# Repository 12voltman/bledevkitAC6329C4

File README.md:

# Dev board for the AC6329C4 from JieLi Tech
Able to be found for an astounding $0.25 in quantity [here](https://www.lcsc.com/product-detail/Microcontroller-Units-MCUs-MPUs-SOCs_JieLi-Tech-AC6329C4_C5440081.html), the AC6329C4 is a promising chip for ultra low cost BLE devices.  
Some of the cool features of this chip:  
- Integrated battery charger
- Integrated LDO for powering peripherals
- BLE 5.3 (may support further with new firmware)
- Full-speed USB OTG with built-in bootloader (needs weird trigger to enter DFU)
- 3 UARTs
- 1 I<sup>2</sup>C
- RTC
- 10-bit ADC w/ 6 channels
## Dev board features
This chip has some oddities around the bootloader, which needs a very specific bit pattern to be presented on the USB lines to enter DFU mode.  To enter DFU mode, I added an ATTINY microcontroller and a USB isolation switch, which also lets you use the USB pins as extra IOs if desired.

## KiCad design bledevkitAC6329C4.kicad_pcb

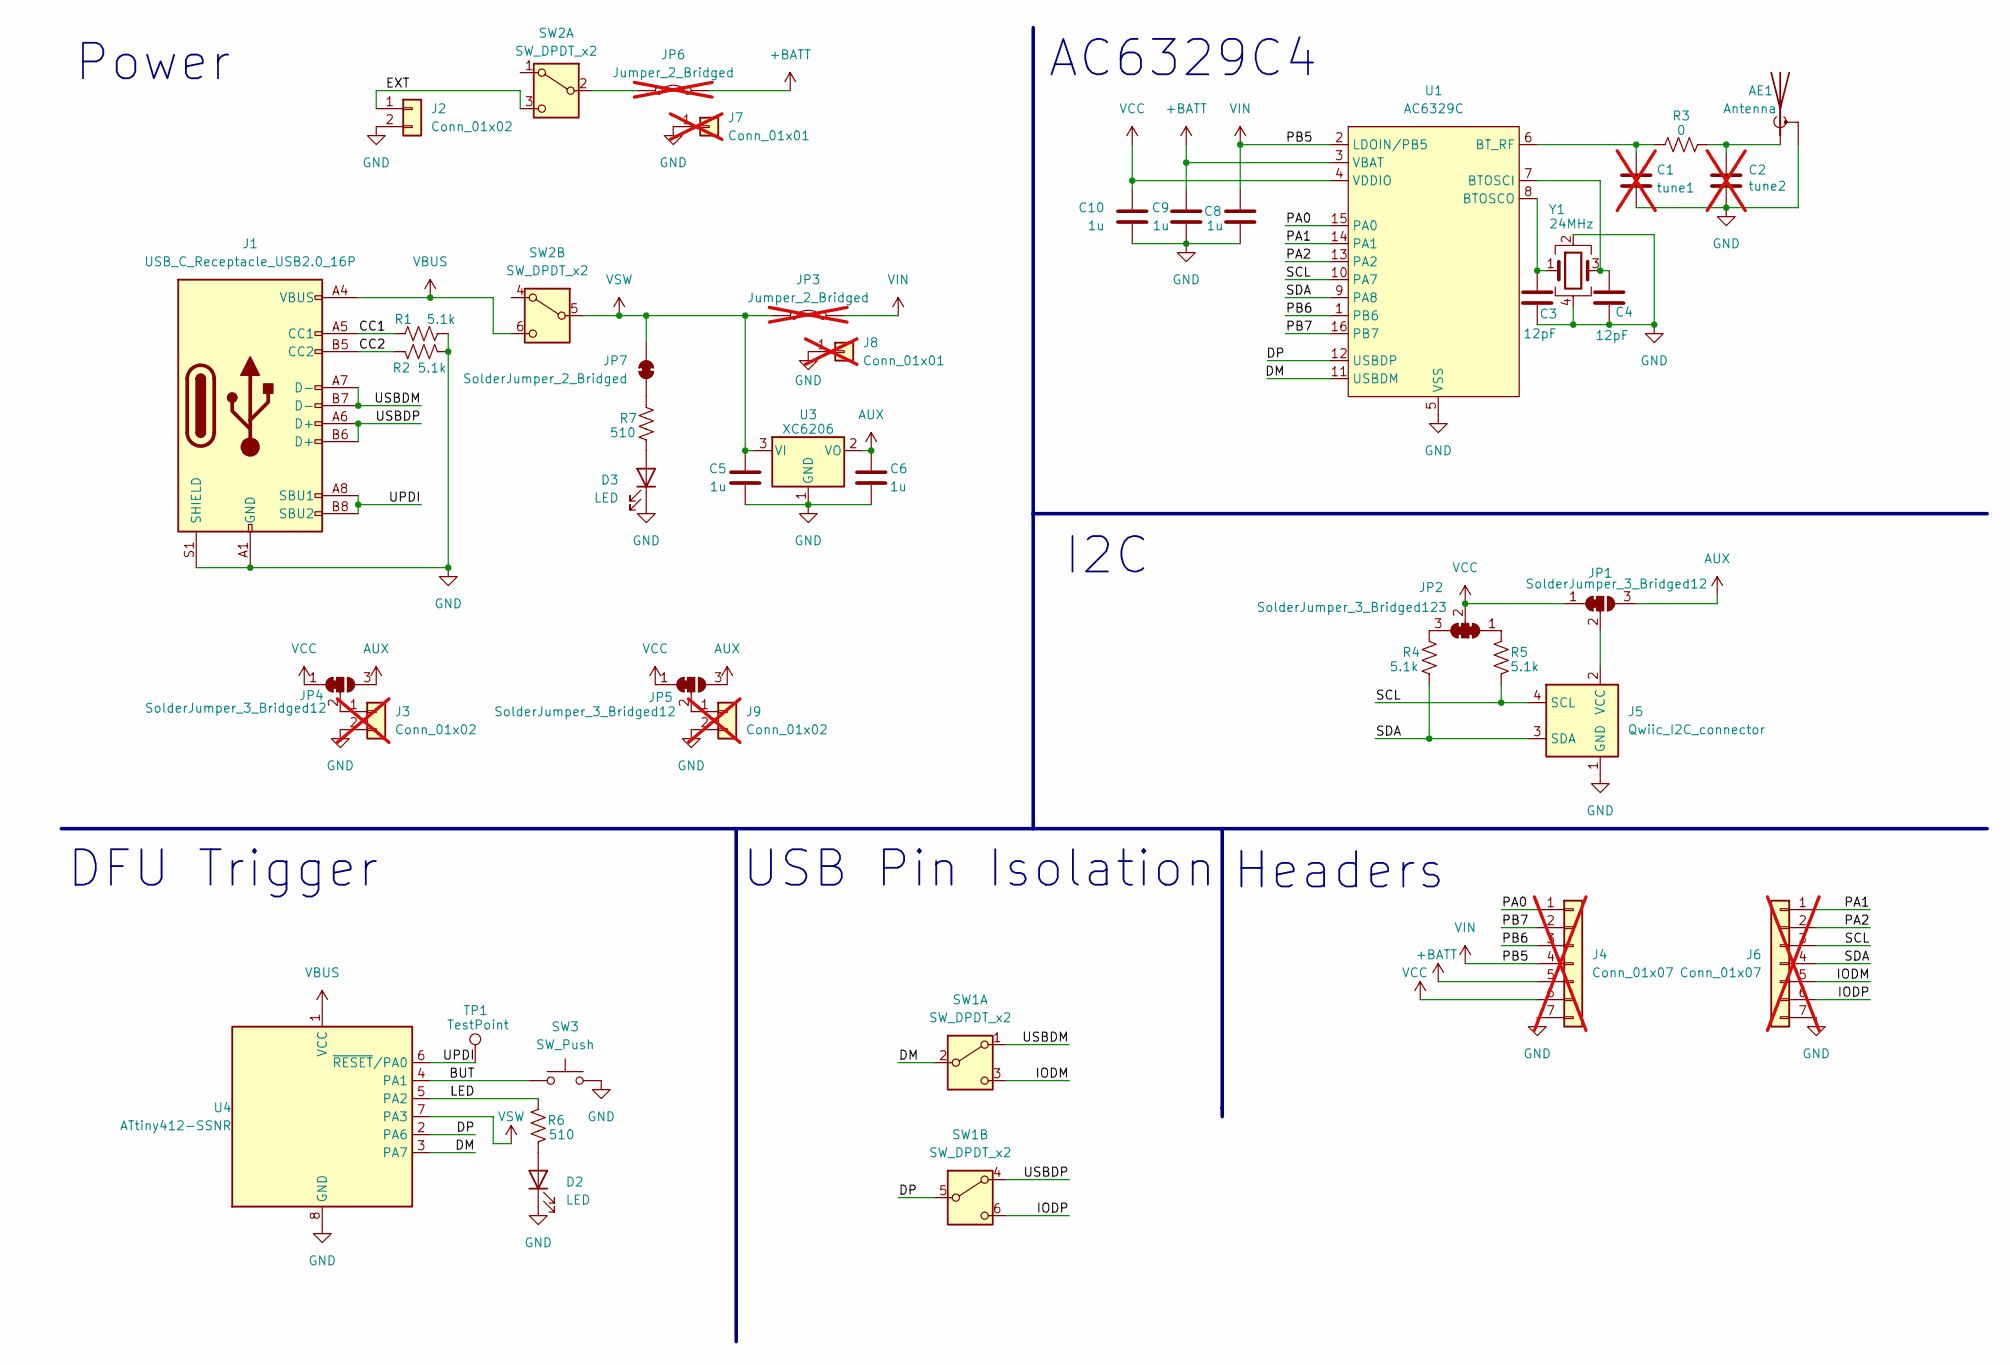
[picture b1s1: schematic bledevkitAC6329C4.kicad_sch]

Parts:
AE1: Antenna; Texas_SWRA117D_2.4GHz_Left
C1: tune1; C_0402_1005Metric; not fitted
C2: tune2; C_0402_1005Metric; not fitted
C3, C4: 12pF; C_0402_1005Metric; LCSC C1547
C5, C6, C8, C9, C10: 1u; C_0402_1005Metric; LCSC C52923
D2: LED; LED_0402_1005Metric; LCSC C2856703
D3: LED; LED_0402_1005Metric; LCSC C965790
J1: USB_C_Receptacle_USB2.0_16P; USB_C_Receptacle_HCTL_HC-TYPE-C-16P-01A; LCSC C2765186
J2: Conn_01x02; JST_PH_S2B-PH-SM4-TB_1x02-1MP_P2.00mm_Horizontal; LCSC C7433648
J3, J9: Conn_01x02; PinHeader_1x02_P2.54mm_Vertical; LCSC C492401; not fitted
J4, J6: Conn_01x07; PinHeader_1x07_P2.54mm_Vertical; LCSC C492406; not fitted
J5: Qwiic_I2C_connector; JST_SH_SM04B-SRSS-TB_1x04-1MP_P1.00mm_Horizontal; LCSC C7433440
J7, J8: Conn_01x01; PinHeader_1x01_P2.54mm_Vertical; LCSC C492400; not fitted
JP1, JP4, JP5: SolderJumper_3_Bridged12; SolderJumper-3_P1.3mm_Bridged12_RoundedPad1.0x1.5mm
JP2: SolderJumper_3_Bridged123; SolderJumper-3_P1.3mm_Bridged123_RoundedPad1.0x1.5mm
JP3, JP6: Jumper_2_Bridged; PinHeader_1x02_P2.54mm_Vertical; LCSC C492401; not fitted
JP7: SolderJumper_2_Bridged; SolderJumper-2_P1.3mm_Bridged_RoundedPad1.0x1.5mm
R1, R2, R4, R5: 5.1k; R_0402_1005Metric; LCSC C25905
R3: 0; R_0402_1005Metric; LCSC C17168
R6, R7: 510; R_0402_1005Metric; LCSC C25123
SW1, SW2: SW_DPDT_x2; DPDT-Slide_top; LCSC C2837066
SW3: SW_Push; TINYTACTILE; LCSC C455280
TP1: TestPoint; TestPoint_Pad_D3.0mm
U1: AC6329C; SOIC-16_3.9x9.9mm_P1.27mm; LCSC C5440081
U3: XC6206; SOT-23-3; LCSC C3015484
U4: ATtiny412-SSNR; SOIC-8_3.9x4.9mm_P1.27mm; LCSC C1337190
Y1: 24MHz; Crystal_SMD_3225-4Pin_3.2x2.5mm; LCSC C70590

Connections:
+BATT: C9.1, J4.5, JP6.2 (B), U1.3 (VBAT)
/BUT: SW3.1, U4.4 (PA1)
/CC1: J1.A5 (CC1), R1.1
/CC2: J1.B5 (CC2), R2.1
/DM: SW1.2 (B), U1.11 (USBDM), U4.3 (PA7)
/DP: SW1.5 (B), U1.12 (USBDP), U4.2 (PA6)
/EXT: J2.1, SW2.3 (C)
/IODM: J6.5, SW1.3 (C)
/IODP: J6.6, SW1.6 (C)
/LED: R6.2, U4.5 (PA2)
/PA0: J4.1, U1.15 (PA0)
/PA1: J6.1, U1.14 (PA1)
/PA2: J6.2, U1.13 (PA2)
/PB6: J4.3, U1.1 (PB6)
/PB7: J4.2, U1.16 (PB7)
/SCL: J5.4 (SCL), J6.3, R5.1, U1.10 (PA7)
/SDA: J5.3 (SDA), J6.4, R4.1, U1.9 (PA8)
/UPDI: J1.A8 (SBU1), J1.B8 (SBU2), TP1.1, U4.6 (~RESET/PA0)
/USBDM: J1.A7 (D-), J1.B7 (D-), SW1.1 (A)
/USBDP: J1.A6 (D+), J1.B6 (D+), SW1.4 (A)
AUX: C6.1, JP1.3 (B), JP4.3 (B), JP5.3 (B), U3.2 (VO)
GND: AE1.2 (Shield), C1.2, C2.2, C3.2, C4.2, C5.2, C6.2, C8.2, C9.2, C10.2, D2.1 (K), D3.1 (K), J1.A1 (GND), J1.A12 (GND), J1.B1 (GND), J1.B12 (GND), J1.S1 (SHIELD), J2.2, J3.2, J4.7, J5.1 (GND), J5.MP (VSS), J6.7, J7.1, J8.1, J9.2, R1.2, R2.2, SW3.2, U1.5 (VSS), U3.1 (GND), U4.8 (GND), Y1.2, Y1.4
unnamed: AE1.1 (A), C2.1, R3.2
unnamed: D2.2 (A), R6.1
unnamed: D3.2 (A), R7.1
unnamed: J3.1, JP4.2 (C)
unnamed: J5.2 (VCC), JP1.2 (C)
unnamed: J9.1, JP5.2 (C)
unnamed: JP2.1 (A), R5.2
unnamed: JP2.3 (B), R4.2
unnamed: JP6.1 (A), SW2.2 (B)
unnamed: JP7.2 (B), R7.2
unnamed: C4.1, U1.7 (BTOSCI), Y1.3
unnamed: C3.1, U1.8 (BTOSCO), Y1.1
unnamed: C1.1, R3.1, U1.6 (BT_RF)
VBUS: J1.A4 (VBUS), J1.A9 (VBUS), J1.B4 (VBUS), J1.B9 (VBUS), SW2.6 (C), U4.1 (VCC)
VCC: C10.1, J4.6, JP1.1 (A), JP2.2 (C), JP4.1 (A), JP5.1 (A), U1.4 (VDDIO)
VIN: C8.1, J4.4, JP3.2 (B), U1.2 (LDOIN/PB5)
VSW: C5.1, JP3.1 (A), JP7.1 (A), SW2.5 (B), U3.3 (VI), U4.7 (PA3)

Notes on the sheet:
DFU Trigger
Power
AC6329C4
I2C
USB Pin Isolation
Headers

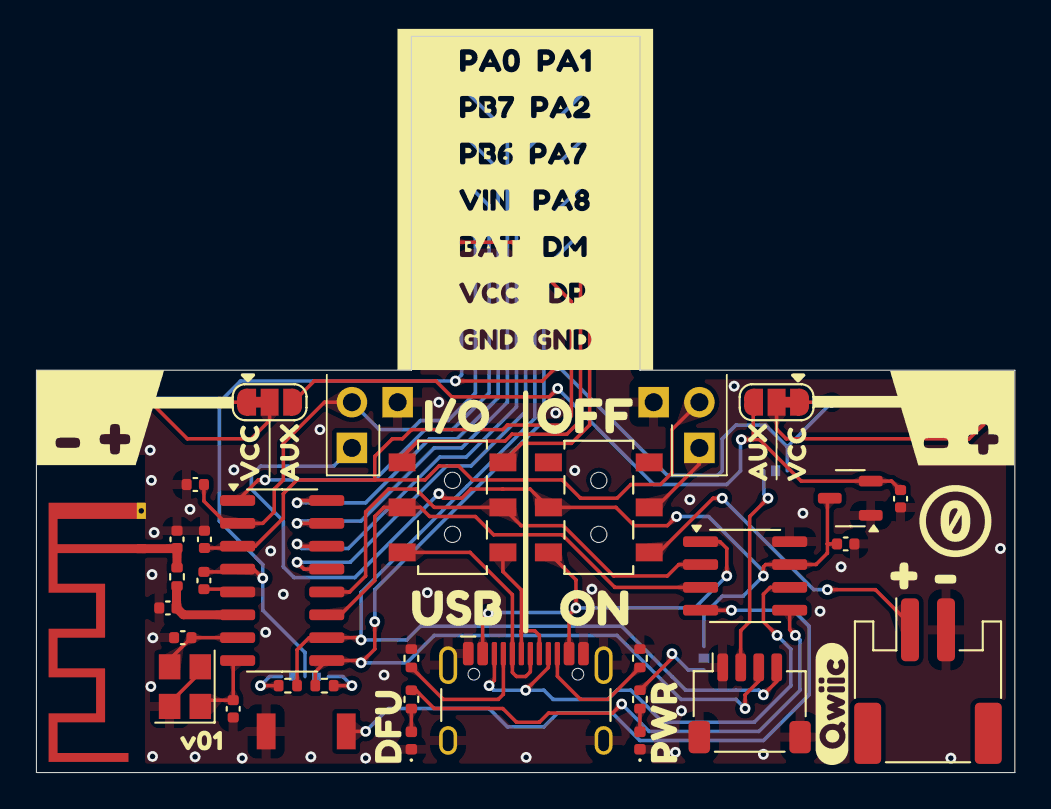
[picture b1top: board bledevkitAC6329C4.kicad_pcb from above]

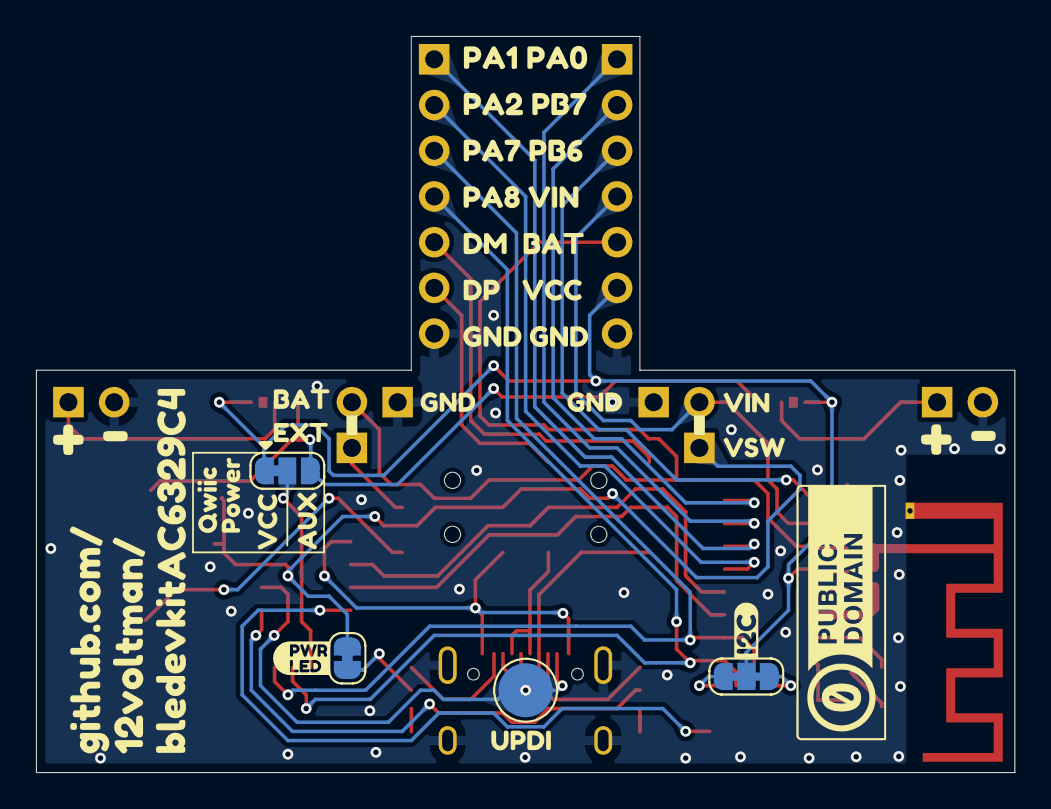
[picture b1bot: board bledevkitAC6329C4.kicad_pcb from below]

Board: 2 copper layers, 54.4 x 40.9 mm, 70 parts (21 on the bottom side), 39 nets.

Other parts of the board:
kibuzzard-667FBBEE: G***; kibuzzard-667FBBEE
kibuzzard-667FBC34: G***; kibuzzard-667FBC34
kibuzzard-6680A94E: G***; kibuzzard-6680A94E
kibuzzard-6680A820: G***; kibuzzard-6680A820
kibuzzard-6680AAC4: G***; kibuzzard-6680AAC4
kibuzzard-6680ABE0: G***; kibuzzard-6680ABE0
kibuzzard-6680AC8C: G***; kibuzzard-6680AC8C
kibuzzard-6680AE53, kibuzzard-6680AE53#2: G***; kibuzzard-6680AE53
kibuzzard-6680B7C1: G***; kibuzzard-6680B7C1
kibuzzard-6680B7CF: G***; kibuzzard-6680B7CF
kibuzzard-6680B177: G***; kibuzzard-6680B177
kibuzzard-6680BA41: G***; kibuzzard-6680BA41
kibuzzard-6680BA59: G***; kibuzzard-6680BA59
kibuzzard-6680BEA0: G***; kibuzzard-6680BEA0
kibuzzard-6680DFC0, kibuzzard-6680DFC0#2: G***; kibuzzard-6680DFC0
kibuzzard-6680E09B: G***; kibuzzard-6680E09B
kibuzzard-66809CDB: G***; kibuzzard-66809CDB
kibuzzard-66809CF2: G***; kibuzzard-66809CF2
kibuzzard-66809D04: G***; kibuzzard-66809D04
kibuzzard-66809D9A: G***; kibuzzard-66809D9A
kibuzzard-66809D18: G***; kibuzzard-66809D18
kibuzzard-66809D78: G***; kibuzzard-66809D78
kibuzzard-66809DBE: G***; kibuzzard-66809DBE
kibuzzard-66809E23, kibuzzard-66809E23#2: G***; kibuzzard-66809E23

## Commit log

2024-06-27 Initial PCB commit WIP
2024-06-28 Finalized power topology
    Isolated all power draws other than AC6329 behind current probe point. Added auxiliary 3.3V regulator as an option for Qwiic header. Shouldn't need any schematic changes, just on to making things fit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
2024-06-29 Finalized switches, chose modern DFU trigger
    Switched to the newest series of the ATTINY line for UPDI programming, which can be done over the USB-C connector for simplicity of flashing. Also made custom footprints for SMD DPDT slide switches. 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
2024-06-30 Finished routing
2024-06-30 Initial BOM and Finalized graphics
2024-06-30 Started DFM optimization
